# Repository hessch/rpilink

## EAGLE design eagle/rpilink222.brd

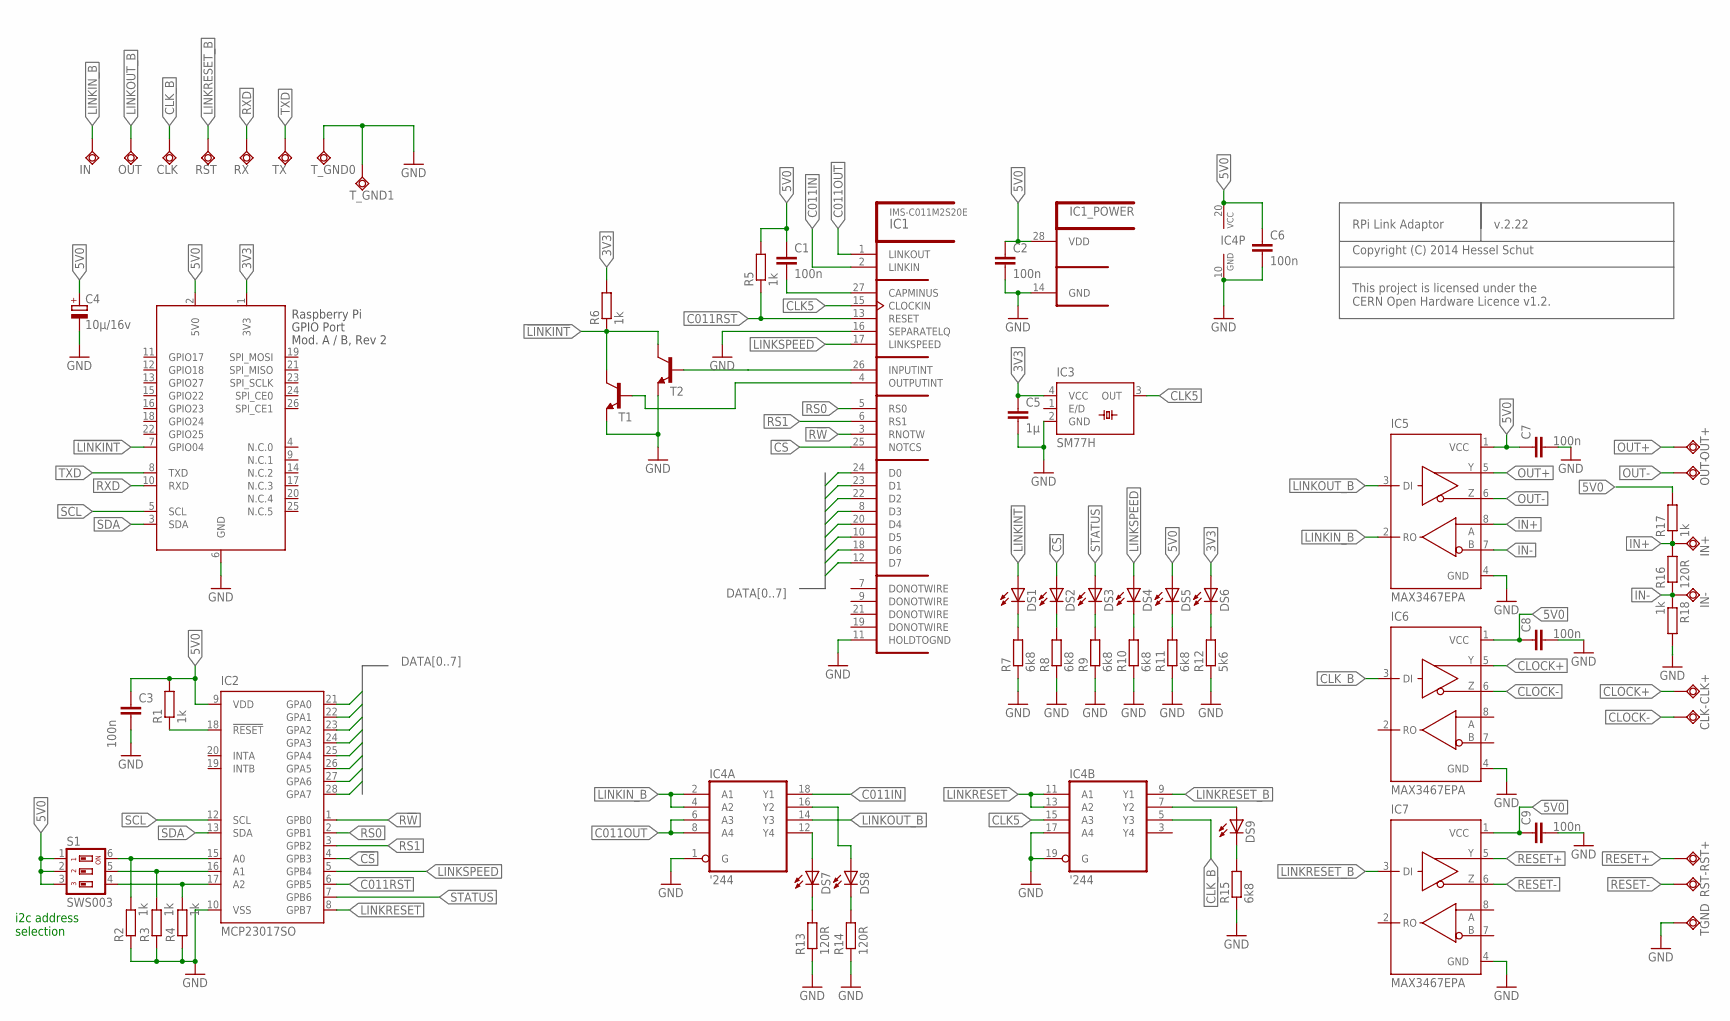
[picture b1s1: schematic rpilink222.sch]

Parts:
C1, C2, C3, C6, C7, C8, C9: 100n; C0805
C4: 10µ/16v; C/6032-28R
C5: 1µ; C0805
CLK: TPSQTP20SQ; TP20SQ
CLK+: TPSQTP20SQ; TP20SQ
CLK-: TPSQTP20SQ; TP20SQ
DS1, DS2, DS3, DS4, DS5, DS6, DS7, DS8, DS9: LEDCHIP-LED0603; CHIP-LED0603
IC1: IMS-C011M2S20E; SOJ28-3
IC2: MCP23017SO; SO28W
IC3: SM77H
IC4: '244; SO20W
IC5, IC6, IC7: MAX3467EPA; SO08
IN: TPSQTP20SQ; TP20SQ
IN+: TPSQTP20SQ; TP20SQ
IN-: TPSQTP20SQ; TP20SQ
OUT: TPSQTP20SQ; TP20SQ
OUT+: TPSQTP20SQ; TP20SQ
OUT-: TPSQTP20SQ; TP20SQ
R1, R2, R3, R4, R5, R6, R17, R18: 1k; R0603
R7, R8, R9, R10, R11, R15: 6k8; R0603
R12: 5k6; R0603
R13, R14, R16: 120R; R0603
RST: TPSQTP20SQ; TP20SQ
RST+: TPSQTP20SQ; TP20SQ
RST-: TPSQTP20SQ; TP20SQ
RX: TPSQTP20SQ; TP20SQ
S1: SWS003; SMS-003
T1, T2: BC808-NPN-SOT23-BEC; SOT23-BEC
TGND: TPSQTP20SQ; TP20SQ
TX: TPSQTP20SQ; TP20SQ
T_GND0, T_GND1: TPSQTP20SQ; TP20SQ
X1: RASPI_BOARD_AB_E2P; RASPI_BOARD_AB_EDGES_2DRILL_PAD

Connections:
3V3: C5.1, DS6.A, IC3.4 (VCC), R6.2, X1.1 (3V3)
5V0: C1.1, C2.1, C3.1, C4.+, C6.1, C7.1, C8.1, C9.1, DS5.A, IC1.28 (VDD), IC2.9 (VDD), IC4.20 (VCC), IC5.1 (VCC), IC6.1 (VCC), IC7.1 (VCC), R1.2, R5.2, R17.2, S1.1, S1.2, S1.3, X1.2 (5V0)
!CS: DS2.A, IC1.25 (NOTCS), IC2.4 (GPB3)
!LINKINT: DS1.A, R6.1, T1.C, T2.C, X1.7 (GPIO04)
C011IN: IC1.2 (LINKIN), IC4.18 (Y1)
C011OUT: IC1.1 (LINKOUT), IC4.6 (A3), IC4.8 (A4)
C011RST: IC1.13 (RESET), IC2.6 (GPB5), R5.1
CLK5: IC1.15 (CLOCKIN), IC3.3 (OUT), IC4.15 (A3)
CLK_B: CLK.TP, IC4.5 (Y3), IC6.3 (DI)
CLOCK+: CLK+.TP, IC6.5 (Y)
CLOCK-: CLK-.TP, IC6.6 (Z)
DATA0: IC1.24 (D0), IC2.21 (GPA0)
DATA1: IC1.23 (D1), IC2.22 (GPA1)
DATA2: IC1.22 (D2), IC2.23 (GPA2)
DATA3: IC1.8 (D3), IC2.24 (GPA3)
DATA4: IC1.20 (D4), IC2.25 (GPA4)
DATA5: IC1.10 (D5), IC2.26 (GPA5)
DATA6: IC1.18 (D6), IC2.27 (GPA6)
DATA7: IC1.12 (D7), IC2.28 (GPA7)
GND: C2.2, C3.2, C4.-, C5.2, C6.2, C7.2, C8.2, C9.2, IC1.11 (HOLDTOGND), IC1.14 (GND), IC1.16 (SEPARATELQ), IC2.10 (VSS), IC3.2 (GND), IC4.1 (G), IC4.10 (GND), IC4.17 (A4), IC4.19 (G), IC5.4 (GND), IC6.4 (GND), IC7.4 (GND), R2.1, R3.1, R4.1, R7.1, R8.1, R9.1, R10.1, R11.1, R12.1, R13.1, R14.1, R15.1, R18.2, T1.E, T2.E, TGND.TP, T_GND0.TP, T_GND1.TP, X1.6 (GND)
IN+: IC5.8 (A), IN+.TP, R16.2, R17.1
IN-: IC5.7 (B), IN-.TP, R16.1, R18.1
LINKIN_B: IC4.2 (A1), IC4.4 (A2), IC5.2 (RO), IN.TP
LINKOUT_B: IC4.14 (Y3), IC5.3 (DI), OUT.TP
LINKRESET: IC2.8 (GPB7), IC4.11 (A1), IC4.13 (A2)
LINKRESET_B: IC4.9 (Y1), IC7.3 (DI), RST.TP
LINKSPEED: DS4.A, IC1.17 (LINKSPEED), IC2.5 (GPB4)
unnamed: IC2.18 (!RESET), R1.1
unnamed: IC2.15 (A0), R2.2, S1.6
unnamed: C1.2, IC1.27 (CAPMINUS)
unnamed: IC2.16 (A1), R3.2, S1.5
unnamed: IC2.17 (A2), R4.2, S1.4
unnamed: IC1.26 (INPUTINT), T2.B
unnamed: IC1.4 (OUTPUTINT), T1.B
unnamed: DS7.C, R13.2
unnamed: DS8.C, R14.2
unnamed: DS7.A, IC4.12 (Y4)
unnamed: DS1.C, R7.2
unnamed: DS2.C, R8.2
unnamed: DS3.C, R9.2
unnamed: DS4.C, R10.2
unnamed: DS5.C, R11.2
unnamed: DS6.C, R12.2
unnamed: DS8.A, IC4.16 (Y2)
unnamed: DS9.A, IC4.7 (Y2)
unnamed: DS9.C, R15.2
OUT+: IC5.5 (Y), OUT+.TP
OUT-: IC5.6 (Z), OUT-.TP
R!W: IC1.3 (RNOTW), IC2.1 (GPB0)
RESET+: IC7.5 (Y), RST+.TP
RESET-: IC7.6 (Z), RST-.TP
RS0: IC1.5 (RS0), IC2.2 (GPB1)
RS1: IC1.6 (RS1), IC2.3 (GPB2)
RXD: RX.TP, X1.10 (RXD)
SCL: IC2.12 (SCL), X1.5 (SCL)
SDA: IC2.13 (SDA), X1.3 (SDA)
STATUS: DS3.A, IC2.7 (GPB6)
TXD: TX.TP, X1.8 (TXD)

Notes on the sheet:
i2c address selection
RPi Link Adaptor
v.2.22
Copyright (C) 2014 Hessel Schut
This project is licensed under the CERN Open Hardware Licence v1.2.

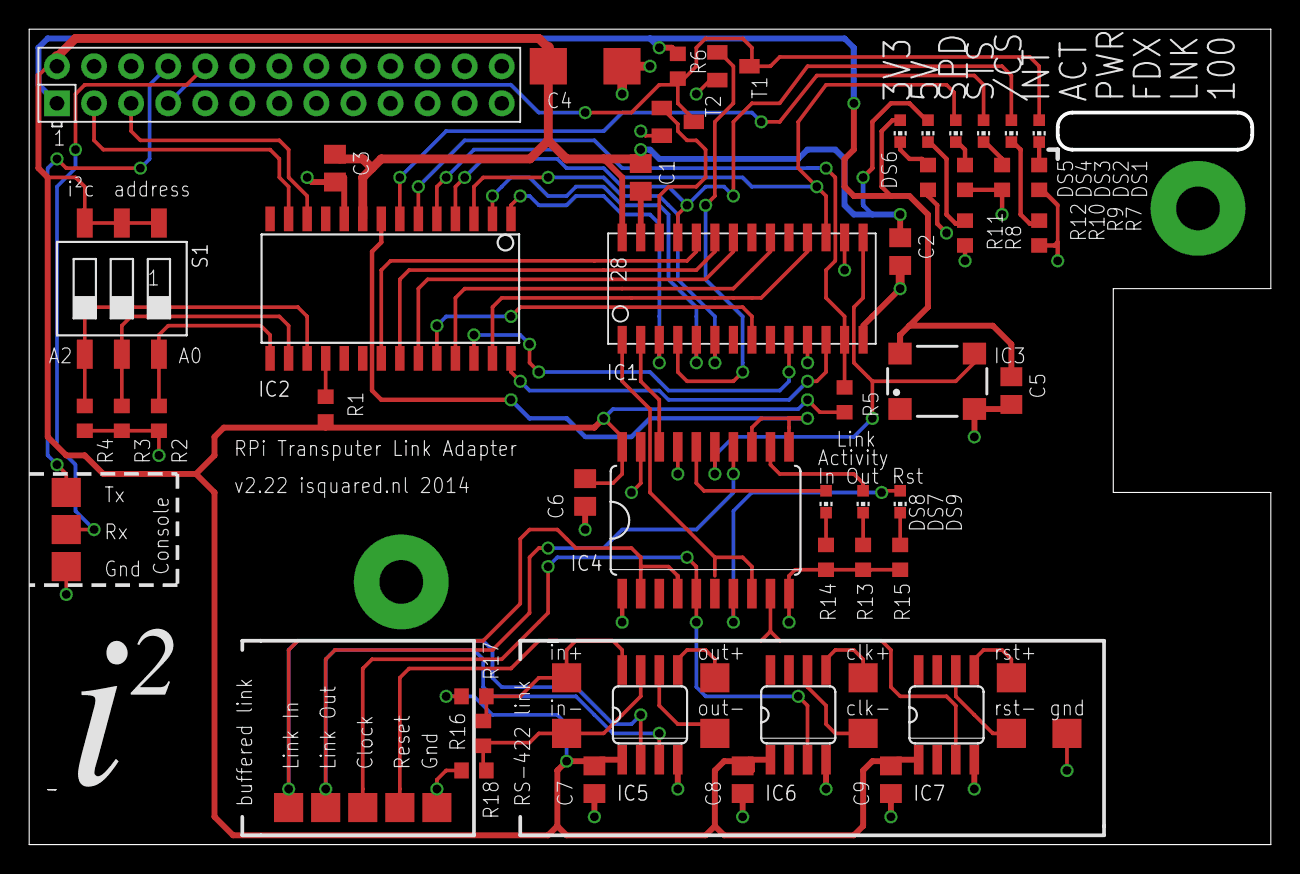
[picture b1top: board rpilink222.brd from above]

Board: 2 copper layers, 84.8 x 55.6 mm, 65 parts (0 on the bottom side), 58 nets.

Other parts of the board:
U$1: LOGOWOBLRG

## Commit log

2014-06-03 added Inmos.py
2014-06-03 allow for multiple links in c011 class
2014-06-28 Addedd proper control pin assignments.
2014-06-28 Dirty write_byte() test.
2014-06-28 Add LED indication to write_byte().
2014-06-28 &|bf
2014-07-04 Led indictaion on reset
2014-07-04 read_byte()
2014-07-04 setup databus for read before asserting notCS
2014-08-12 minor changes
2014-08-19 added in/out status reg access
2014-08-20 added setsignal
2014-08-20 fixes to setsignal
2014-09-02 Rewrite for MCP23017.
2014-10-12 Added simple test for Inmos2.py
2014-10-13 Added link status register tests: is_data_present() and is_output_ready().
2014-10-17 Fixed copy-paste boo boo.
2014-10-17 Added documentation, minor changes.
2014-10-17 Added enable_interrupts()
2014-10-17 Added disable_interrupts() as a companion to enable_interrupts().
2014-10-21 Added tdetect.py.
2014-10-21 Typo & doc fixes.
2014-10-29 minor fix
2014-10-29 Added link echo test.
2014-10-31 tdetect fixes
2014-11-03 dropped is_ from is_output_read() and is_data_present()
2014-11-06 Added Eagle files. Moved linktest and tdetect to utils.
2014-11-06 PCB pictures added
2014-11-06 Updated signals for board version 2.22. Added link reset.
2014-11-06 Rename Inmos2 -> Inmos, old code deleted.
2014-11-06 moved docs
2014-11-06 rename
2014-11-07 Added GPL license.
2014-11-07 Added OHL license.
2014-11-07 Added CERN_OHR license information.
2014-11-13 Added component values, added rs-422 bias resistors.
2014-11-16 some formatting fixes
2014-11-16 change link_speed to linkspeed
2014-11-16 usb cut-out
2015-03-28 link was used before definition
